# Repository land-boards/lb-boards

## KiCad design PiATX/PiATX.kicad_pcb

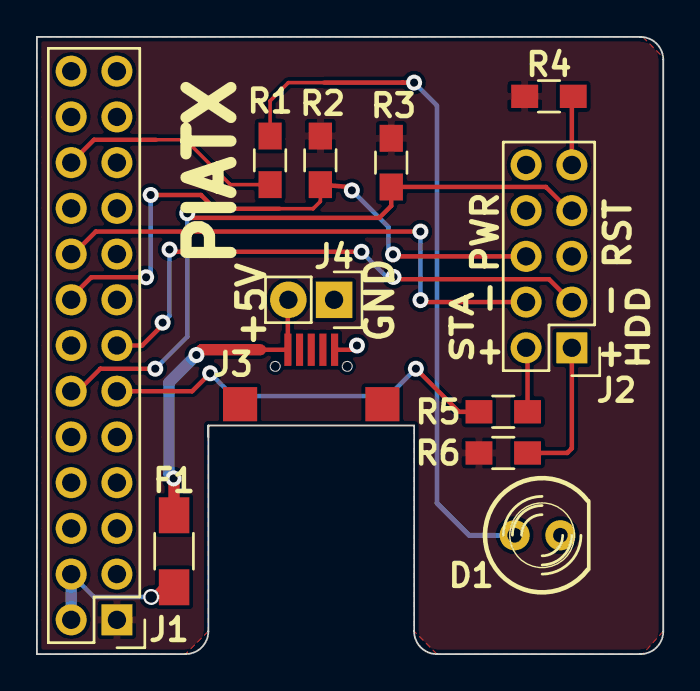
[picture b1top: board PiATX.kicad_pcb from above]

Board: 2 copper layers, 34.8 x 34.3 mm, 12 parts (0 on the bottom side), 14 nets.

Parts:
D1: LED; LED-5MM
F1: FUSE; R_1206_HandSoldering
J1: RASPIO; Pin_Header_Straight_2x13
J2: CONN_02X05; Pin_Header_Straight_2x05
J3: USB-MICRO-B; USB_Micro-B-Wellco-SMT
J4: CONN_01X02; Pin_Header_Straight_1x02
R1, R5, R6: 120; R_0805_HandSoldering
R2, R3: 2.2K; R_0805_HandSoldering
R4: DNP; R_0805_HandSoldering

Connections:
+3V3: J1.1, R2.2, R3.2, R4.2, R6.2
+5V: F1.1, J1.2, J1.4
/FP_PWR_SLP_1: J1.11, R5.1
/FP_PWR_SLP_2: J1.18, J2.4
/HDACT: J1.13, J2.3
/HD_LED_P: J2.1, R6.1
/PWR_SW_P: J1.16, J2.6, R2.1
/RST_SW_P: J1.12, J2.7, R3.1
GND: D1.2, J1.6, J1.9, J1.14, J1.20, J1.25, J2.5, J2.8, J3.5, J4.1
unnamed: D1.1, R1.1
unnamed: F1.2, J3.1, J4.2
unnamed: J1.22, R1.2
unnamed: J2.2, R5.2
unnamed: J2.9, R4.1

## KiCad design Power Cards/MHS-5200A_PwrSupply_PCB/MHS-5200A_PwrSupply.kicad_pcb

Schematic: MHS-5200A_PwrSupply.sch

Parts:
B1: COUPON; BD-49X49
C1, C2: 1200uF; CP_Radial_Tantal_D10.5mm_P5.00mm
C3, C5: 0.1uF; C_Axial_L5.1mm_D3.1mm_P10.00mm_Horizontal
C4: CP1; CP_Radial_Tantal_D10.5mm_P5.00mm
D1, D2, D3, D4: DIODESCH-fixed; D_DO-201AD_P15.24mm_Horizontal
J1, J2: Conn_01x02; TB2-5MM
U1: LF50_TO220; TO-220-3_Vertical

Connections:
/5V: C4.1, C5.1, J2.2, U1.3 (VO)
/GND: C1.2, C2.2, C3.2, C4.2, C5.2, D1.2, D2.2, J2.1, U1.2 (GND)
/VDC: C1.1, C2.1, C3.1, D3.1, D4.1, U1.1 (VI)
unnamed: D1.1, D3.2, J1.1
unnamed: D2.1, D4.2, J1.2

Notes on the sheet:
AC IN
DC OUT

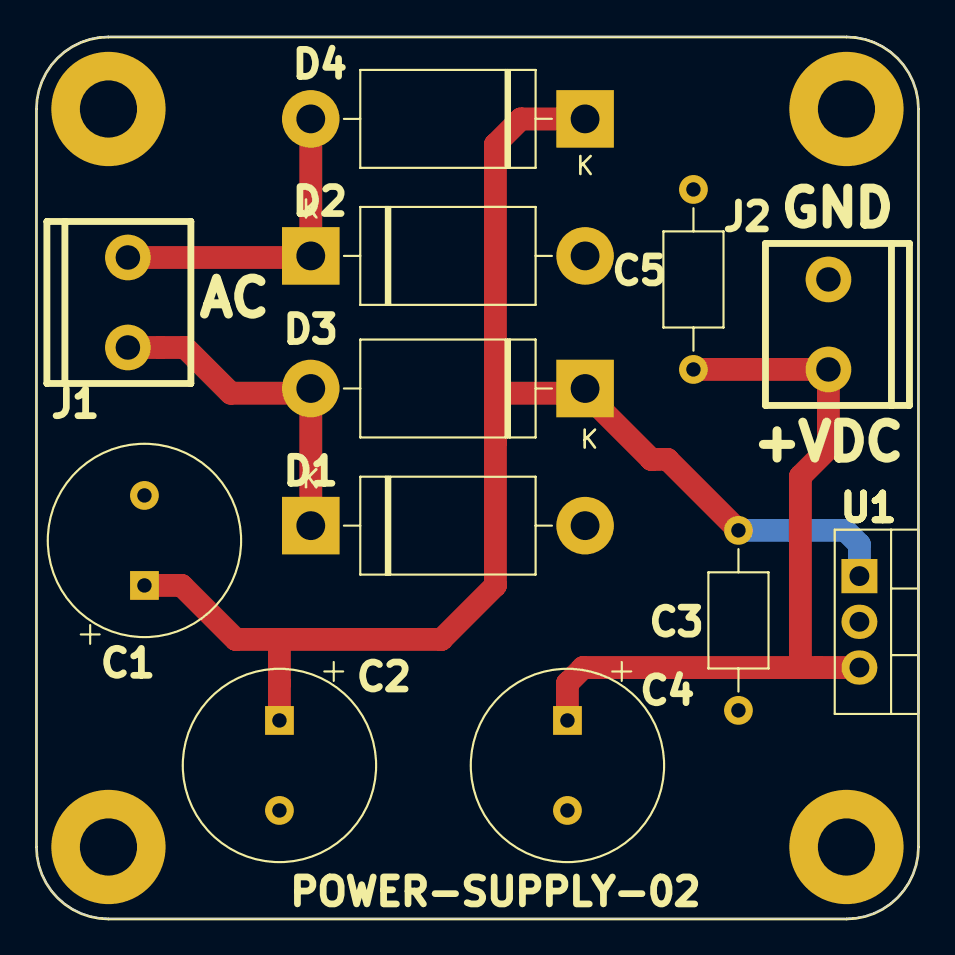
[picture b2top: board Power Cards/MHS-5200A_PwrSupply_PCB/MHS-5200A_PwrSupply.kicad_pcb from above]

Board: 2 copper layers, 49.0 x 49.0 mm, 13 parts (0 on the bottom side), 5 nets.

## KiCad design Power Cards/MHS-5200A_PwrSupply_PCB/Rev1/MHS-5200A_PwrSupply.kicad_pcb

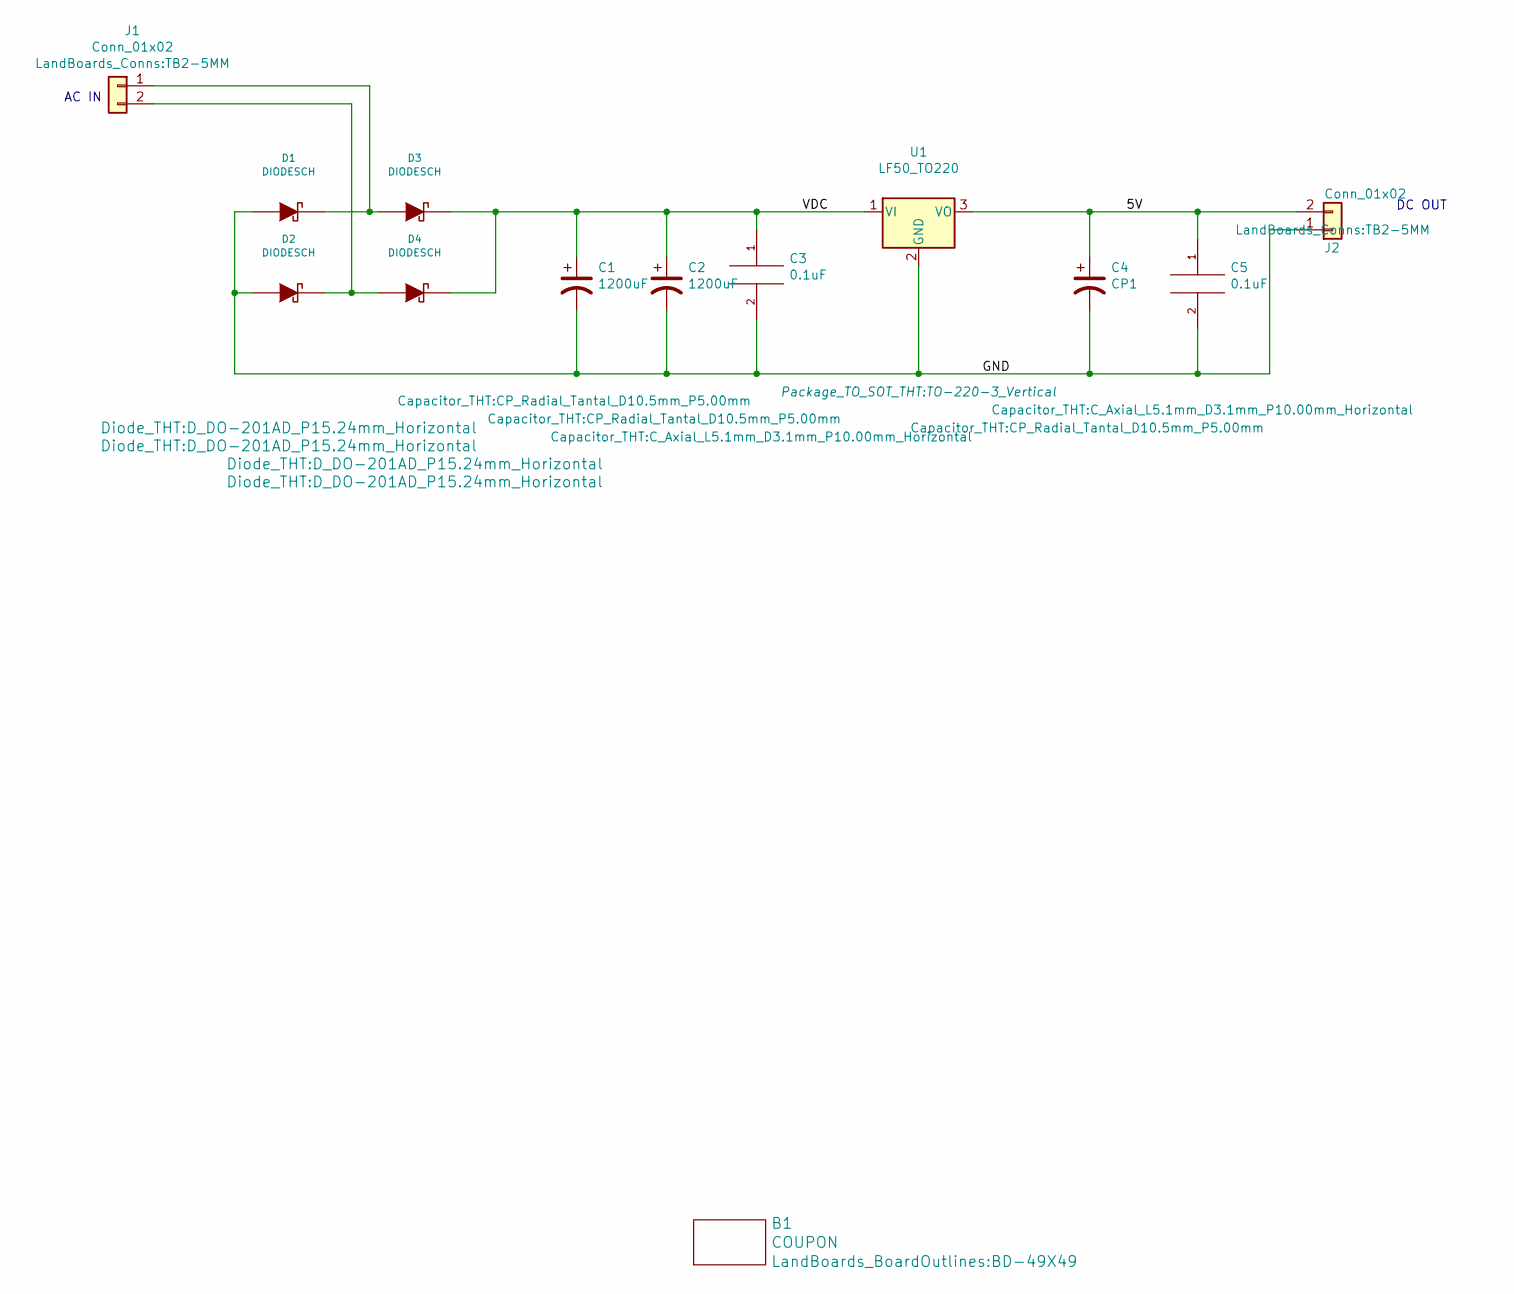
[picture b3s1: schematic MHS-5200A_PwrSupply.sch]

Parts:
B1: COUPON; BD-49X49
C1, C2: 1200uF; CP_Radial_Tantal_D10.5mm_P5.00mm
C3, C5: 0.1uF; C_Axial_L5.1mm_D3.1mm_P10.00mm_Horizontal
C4: CP1; CP_Radial_Tantal_D10.5mm_P5.00mm
D1, D2, D3, D4: DIODESCH; D_DO-201AD_P15.24mm_Horizontal
J1, J2: Conn_01x02; TB2-5MM
U1: LF50_TO220; TO-220-3_Vertical

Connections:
/5V: C4.1, C5.1, J2.2, U1.3 (VO)
/GND: C1.2, C2.2, C3.2, C4.2, C5.2, D1.1 (A), D2.1 (A), J2.1, U1.2 (GND)
/VDC: C1.1, C2.1, C3.1, D3.2 (K), D4.2 (K), U1.1 (VI)
unnamed: D1.2 (K), D3.1 (A), J1.1
unnamed: D2.2 (K), D4.1 (A), J1.2

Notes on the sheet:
AC IN
DC OUT

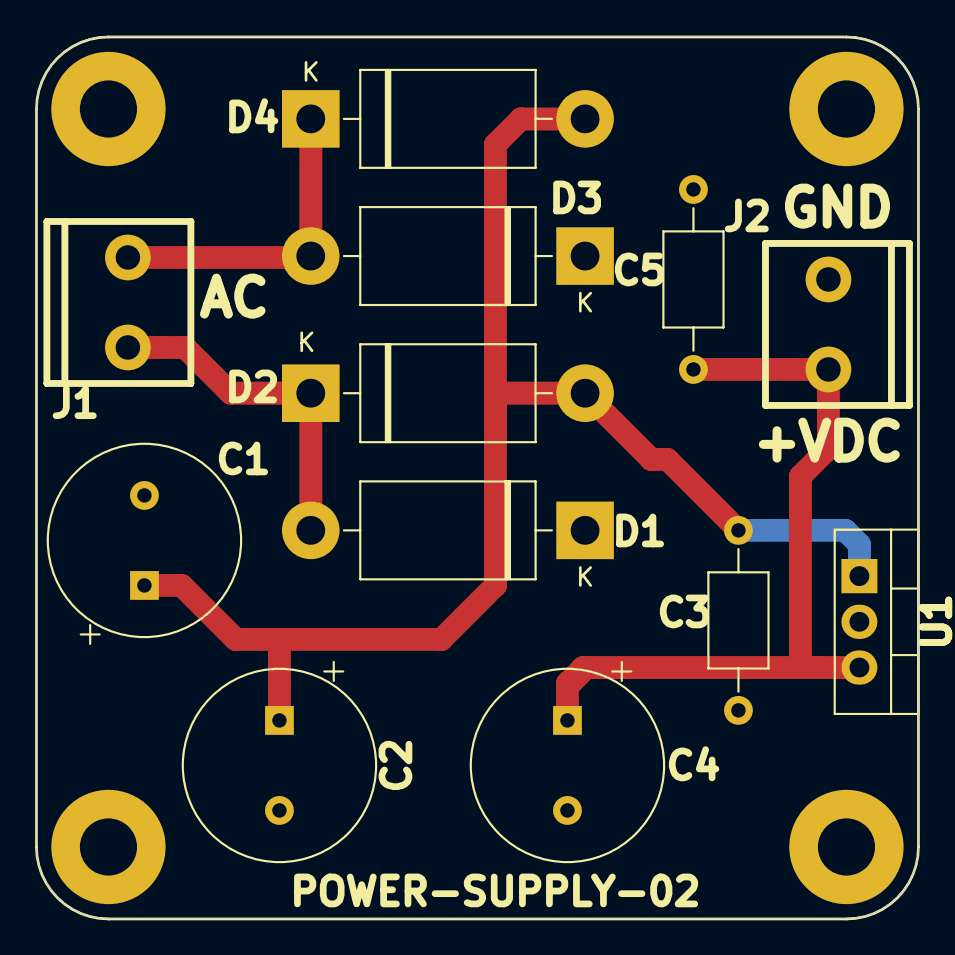
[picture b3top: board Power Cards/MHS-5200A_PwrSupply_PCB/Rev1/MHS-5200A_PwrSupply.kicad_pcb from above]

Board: 2 copper layers, 49.0 x 49.0 mm, 13 parts (0 on the bottom side), 5 nets.

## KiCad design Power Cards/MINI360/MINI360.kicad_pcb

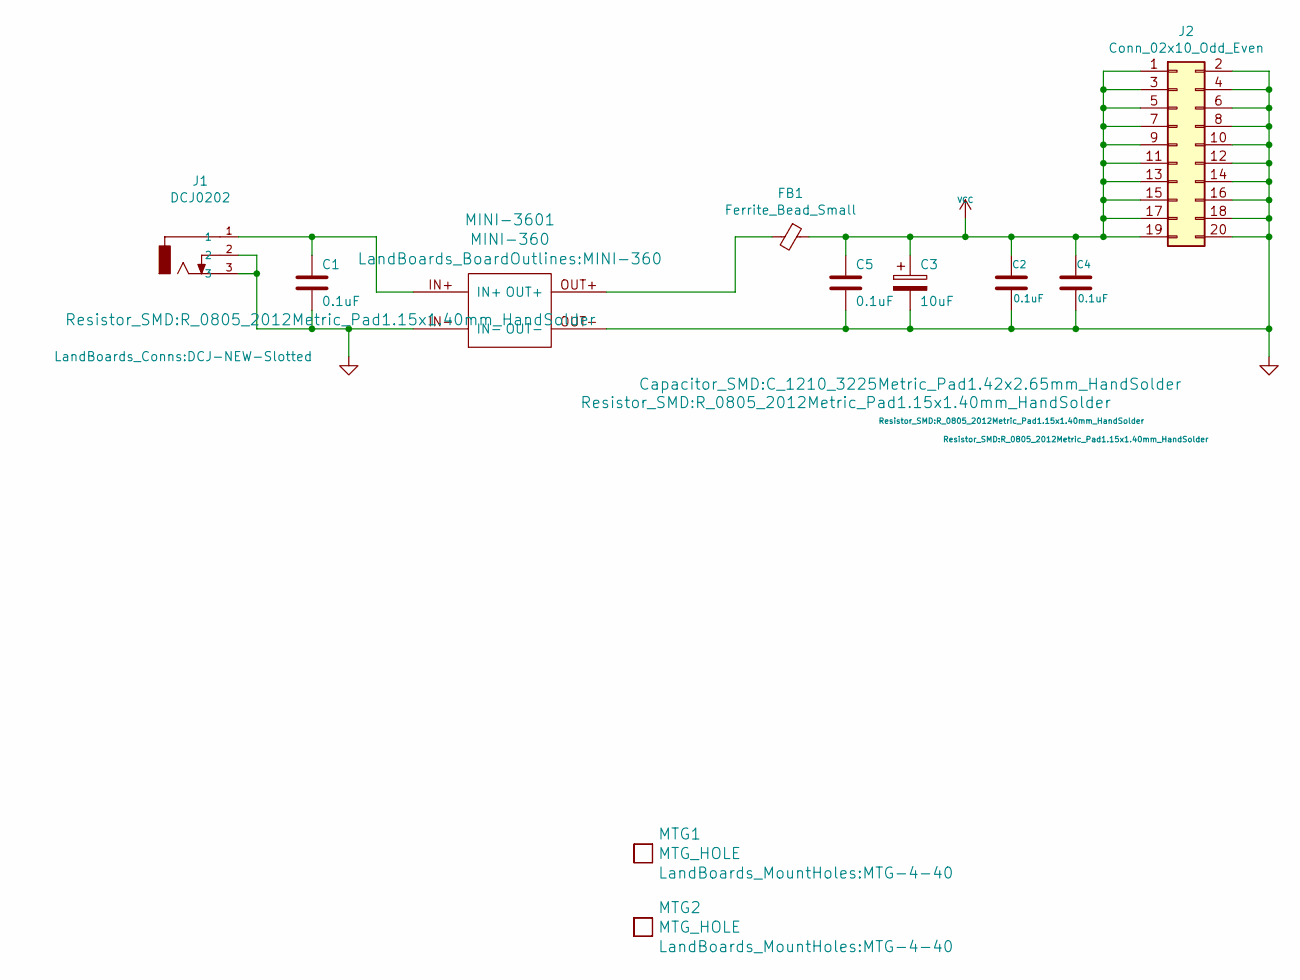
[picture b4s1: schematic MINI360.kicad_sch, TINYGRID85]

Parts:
C1, C2, C4, C5: 0.1uF; R_0805_2012Metric_Pad1.15x1.40mm_HandSolder
C3: 10uF; C_1210_3225Metric_Pad1.42x2.65mm_HandSolder
FB1: Ferrite_Bead_Small; L_0805_2012Metric_Pad1.15x1.40mm_HandSolder
J1: DCJ0202; DCJ-NEW-Slotted
J2: Conn_02x10_Odd_Even; PinHeader_2x10_P2.54mm_Vertical
MINI-3601: MINI-360
MTG1, MTG2: MTG_HOLE; MTG-4-40

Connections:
GND: C1.2, C2.2, C3.2, C4.2, C5.2, J1.2, J1.3, J2.2, J2.4, J2.6, J2.8, J2.10, J2.12, J2.14, J2.16, J2.18, J2.20, MINI-3601.IN-, MINI-3601.OUT-; also elsewhere on the board
unnamed 1: C1.1, J1.1, MINI-3601.IN+; also elsewhere on the board
unnamed 2: FB1.2, MINI-3601.OUT+; also elsewhere on the board
VCC: C2.1, C3.1, C4.1, C5.1, FB1.1, J2.1, J2.3, J2.5, J2.7, J2.9, J2.11, J2.13, J2.15, J2.17, J2.19

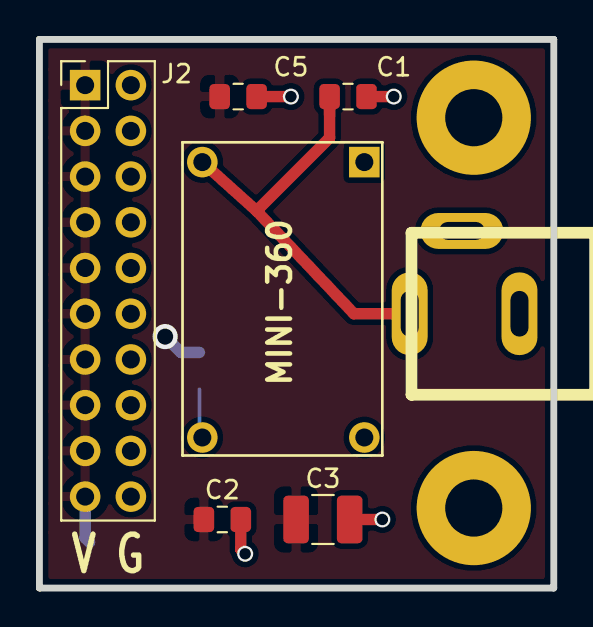
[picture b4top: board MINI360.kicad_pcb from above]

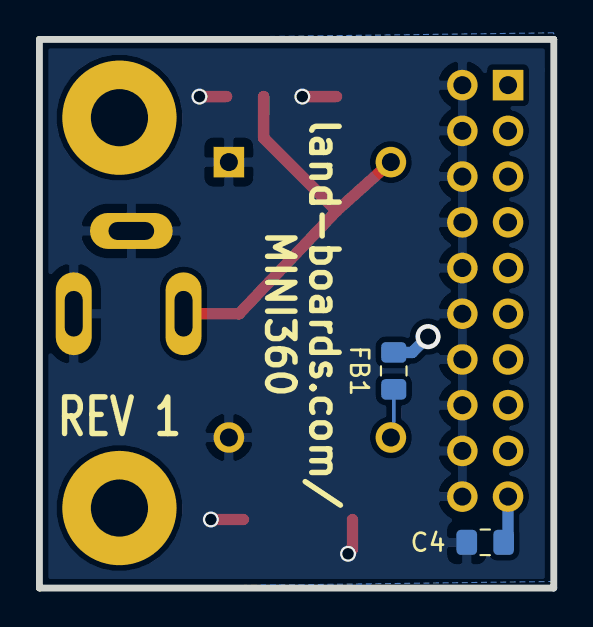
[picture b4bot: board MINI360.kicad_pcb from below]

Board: 2 copper layers, 28.6 x 30.5 mm, 11 parts (2 on the bottom side), 4 nets.

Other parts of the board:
MINI-360: MINI-360

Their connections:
GND: MINI-360.IN-, MINI-360.OUT-; also elsewhere on the board
unnamed 1: MINI-360.IN+; also elsewhere on the board
unnamed 2: MINI-360.OUT+; also elsewhere on the board

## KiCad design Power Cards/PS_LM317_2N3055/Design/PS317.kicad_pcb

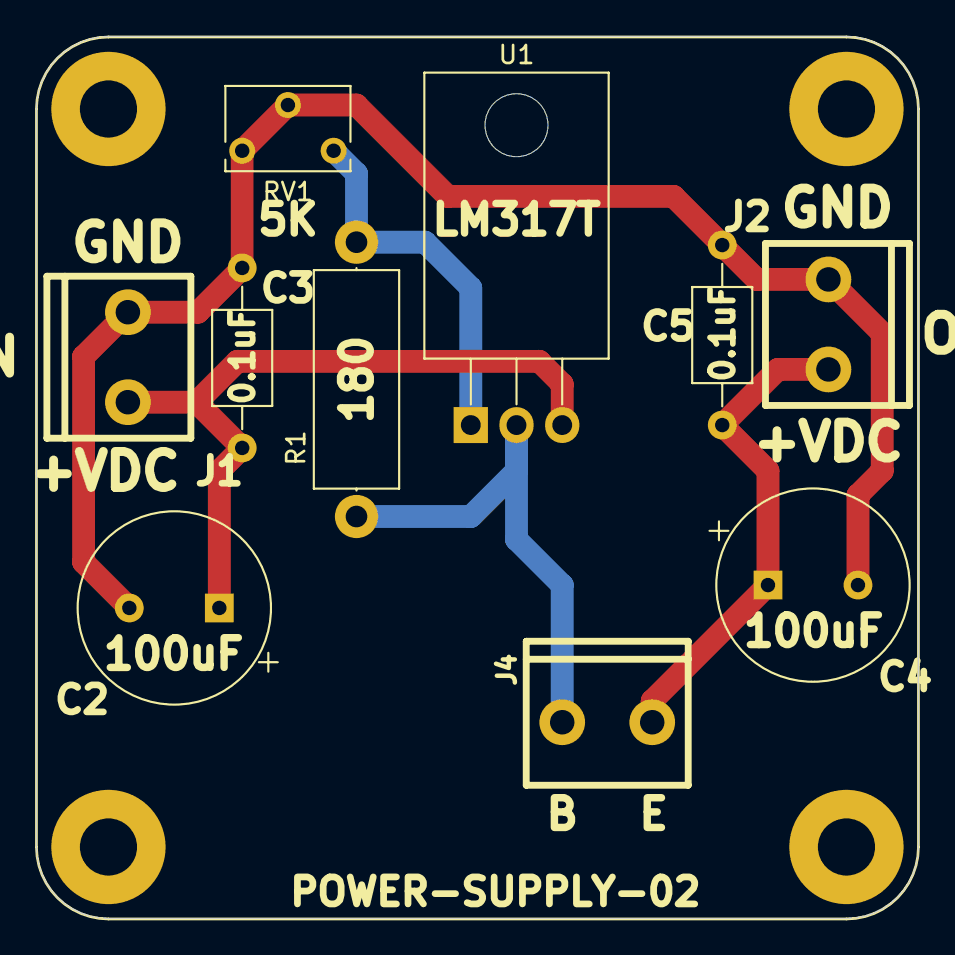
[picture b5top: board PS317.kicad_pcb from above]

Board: 2 copper layers, 49.0 x 49.0 mm, 11 parts (0 on the bottom side), 5 nets.

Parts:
B1: COUPON; BD-49X49
C2: 10uF; CP_Radial_Tantal_D10.5mm_P5.00mm
C3, C5: 0.1uF; C_Axial_L5.1mm_D3.1mm_P10.00mm_Horizontal
C4: 100uF; CP_Radial_Tantal_D10.5mm_P5.00mm
J1, J2, J4: Conn_01x02; TB2-5MM
R1: 180; R_Axial_DIN0414_L11.9mm_D4.5mm_P15.24mm_Horizontal
RV1: 5K; Potentiometer_Bourns_3266W_Vertical
U1: LM317T_TO220; TO-220-3_Horizontal_TabDown

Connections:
/ADJ: R1.2, RV1.3, U1.1
/B: J4.1, R1.1, U1.2
/GND: C2.2, C3.2, C4.2, C5.2, J1.2, J2.1, RV1.1, RV1.2
/Vin: C2.1, C3.1, J1.1, U1.3
/Vout: C4.1, C5.1, J2.2, J4.2

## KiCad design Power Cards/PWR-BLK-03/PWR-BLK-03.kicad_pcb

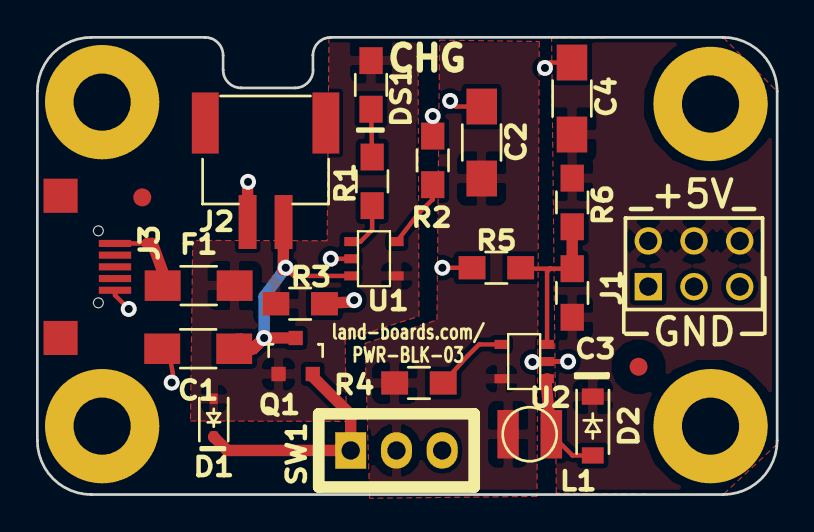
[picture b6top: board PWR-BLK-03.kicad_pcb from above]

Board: 2 copper layers, 41.1 x 25.4 mm, 28 parts (0 on the bottom side), 13 nets.

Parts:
C1: 10uF; R_1206_HandSoldering
C2, C4: 4.7uF; R_1206_HandSoldering
C3: 680pF; R_0805_HandSoldering
D1: D_Schottky_FixedPinout; SOD-323
D2: MBR0520LT1G; SOD-123-FIXED
DS1: LED; R_0805_HandSoldering
F1: FUSE; R_1206_HandSoldering
FID1, FID2: CONN_1; FIDUCIAL
J1: CONN_3X2; PIN_ARRAY_3X2
J2: JST_2; JST-2-SMT
J3: USB-MICRO-B; USB_Micro-B-Wellco-SMT
L1: 10uH; IND-3MM
MTG1, MTG2, MTG3, MTG4: CONN_1; MTG-4-40
Q1: PMV48XP; SOT-23
R1: 470; R_0805_HandSoldering
R2: 2.2K; R_0805_HandSoldering
R3: 10K; R_0805_HandSoldering
R4: 1M; R_0805_HandSoldering
R5: 1K; R_0805_HandSoldering
R6: 3.09K; R_0805_HandSoldering
SW1: Switch_SPDT_x2; SPDT0.1IN
U1: MCP73831; SOT23-5
U2: LMR62014; SOT23-5

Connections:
/5V Power Supply/3.7V: C2.1, L1.1, R4.1, SW1.2, U2.5
/5V Power Supply/+5VOUT: C3.2, C4.1, D2.2, J1.2, J1.4, J1.6, R6.2
/5V Power Supply/VFB: D2.1, L1.2, U2.1
/LiPo Battery Charger/VB-3.7: D1.1, Q1.2, SW1.1
/USB/+5VUSB: D1.2, DS1.1, F1.2, Q1.1, R3.1, U1.4
GND: C1.2, C2.2, C4.2, J1.1, J1.3, J1.5, J2.1, J3.5, R2.2, R3.2, R5.2, U1.2, U2.2
unnamed: C1.1, J2.2, Q1.3, U1.3
unnamed: C3.1, R5.1, R6.1, U2.3
unnamed: DS1.2, R1.2
unnamed: F1.1, J3.1
unnamed: R1.1, U1.1
unnamed: R2.1, U1.5
unnamed: R4.2, U2.4

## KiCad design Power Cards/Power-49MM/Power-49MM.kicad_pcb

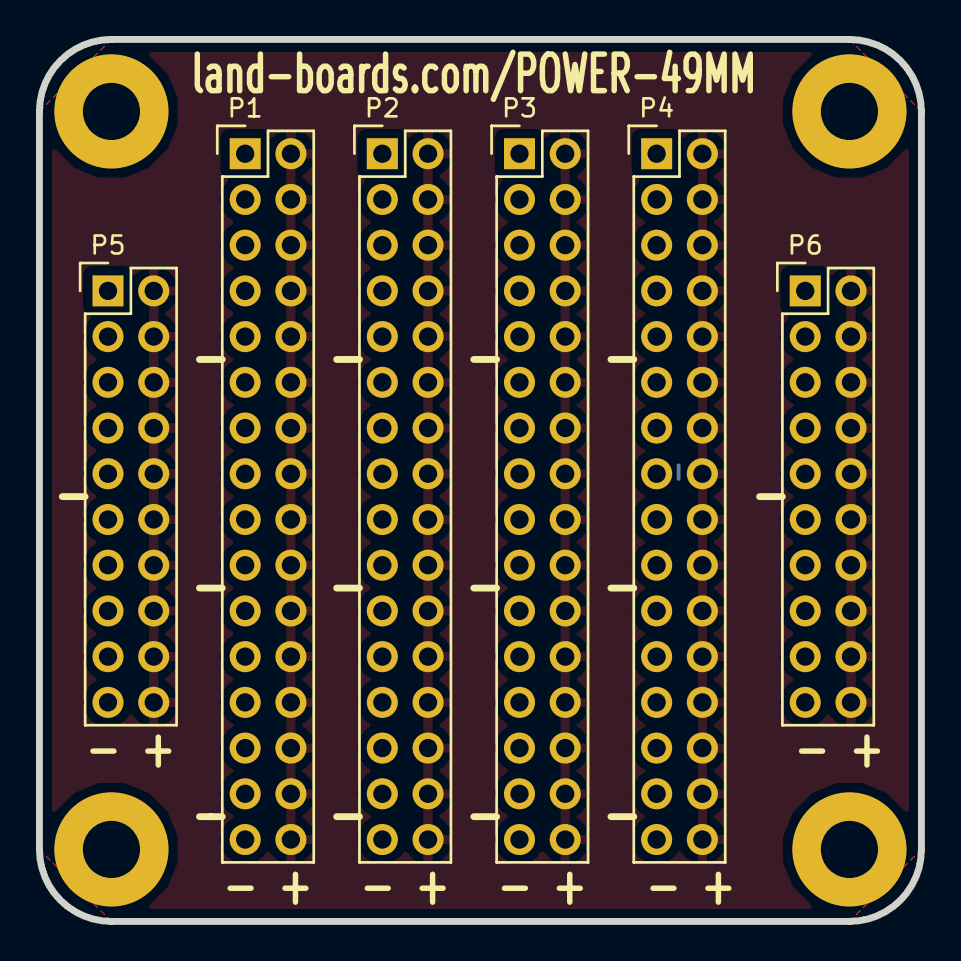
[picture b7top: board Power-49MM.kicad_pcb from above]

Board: 2 copper layers, 49.0 x 49.0 mm, 10 parts (0 on the bottom side), 2 nets.

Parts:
MTG1, MTG2, MTG3, MTG4: CONN_1; MTG-4-40
P1, P2, P3, P4: CONN_02X16; Pin_Header_Straight_2x16
P5, P6: CONN_02X10; Pin_Header_Straight_2x10

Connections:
/GND: P1.1, P1.3, P1.5, P1.7, P1.9, P1.11, P1.13, P1.15, P1.17, P1.19, P1.21, P1.23, P1.25, P1.27, P1.29, P1.31, P2.1, P2.3, P2.5, P2.7, P2.9, P2.11, P2.13, P2.15, P2.17, P2.19, P2.21, P2.23, P2.25, P2.27, P2.29, P2.31, P3.1, P3.3, P3.5, P3.7, P3.9, P3.11, P3.13, P3.15, P3.17, P3.19, P3.21, P3.23, P3.25, P3.27, P3.29, P3.31, P4.1, P4.3, P4.5, P4.7, P4.9, P4.11, P4.13, P4.15, P4.17, P4.19, P4.21, P4.23, P4.25, P4.27, P4.29, P4.31, P5.1, P5.3, P5.5, P5.7, P5.9, P5.11, P5.13, P5.15, P5.17, P5.19, P6.1, P6.3, P6.5, P6.7, P6.9, P6.11, P6.13, P6.15, P6.17, P6.19
/VCC: P1.2, P1.4, P1.6, P1.8, P1.10, P1.12, P1.14, P1.16, P1.18, P1.20, P1.22, P1.24, P1.26, P1.28, P1.30, P1.32, P2.2, P2.4, P2.6, P2.8, P2.10, P2.12, P2.14, P2.16, P2.18, P2.20, P2.22, P2.24, P2.26, P2.28, P2.30, P2.32, P3.2, P3.4, P3.6, P3.8, P3.10, P3.12, P3.14, P3.16, P3.18, P3.20, P3.22, P3.24, P3.26, P3.28, P3.30, P3.32, P4.2, P4.4, P4.6, P4.8, P4.10, P4.12, P4.14, P4.16, P4.18, P4.20, P4.22, P4.24, P4.26, P4.28, P4.30, P4.32, P5.2, P5.4, P5.6, P5.8, P5.10, P5.12, P5.14, P5.16, P5.18, P5.20, P6.2, P6.4, P6.6, P6.8, P6.10, P6.12, P6.14, P6.16, P6.18, P6.20
